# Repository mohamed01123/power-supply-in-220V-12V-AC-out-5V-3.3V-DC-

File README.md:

Universal Power Supply Circuit

This project is an electronic power supply circuit that can be powered by either 12V (AC or DC) or 220V AC, and outputs regulated 5V or 3.3V DC. It includes input protection, voltage regulation, and indicators for status and output selection.

🧩 Features
Dual Input Power:
220V AC (via HLK-PM12 module)
12V input (can be AC or DC)
Selectable Output:
5V or 3.3V regulated DC output
Power Mode Switch:
Toggle between AC or DC mode using a manual switch
Safety Features:
Diodes for reverse polarity protection (especially for 12V DC input)
Bridge rectifier to convert 12V AC to DC
Status Indicator:
LED to indicate that the circuit is powered ON

🔌 Circuit Components
HLK-PM12 : AC-DC module to convert 220V AC to 12V DC
Bridge Rectifier: Converts 12V AC input to DC
7805 Regulator: Outputs regulated 5V
7833 Regulator: Outputs regulated 3.3V
2x Electrolytic Capacitors: For filtering and stabilizing DC output
2x Protection Diodes: Prevents damage if user reverses DC input polarity
Power Mode Switch: Selects between AC and DC input modes
Output Selector Socket: Allows user to choose between 5V and 3.3V output
3x Sockets: 1 for 220V AC input, 1 for 12V input (AC/DC), 1 for output
Power Indicator LED: Lights up when power is supplied to the circuit

⚙️ Working Principle
1-Input:
  If using 220V AC, the circuit powers through HLK-PM12, which outputs 12V DC.
  If using 12V, it can be AC or DC:
  AC: Passed through a bridge rectifier.
  DC: Goes directly to the regulators, with diode protection in case of reversed polarity.
2-Stabilization:
  Capacitors filter and stabilize the voltage before reaching the regulators.
  Output Regulation:
  You can select between 5V (via 7805) or 3.3V (via 7833) using a selector socket.
3-LED Indicator:
  A simple LED indicates that the circuit is powered and active.

🛠️ Use Cases
Powering microcontrollers (like Arduino or ESP8266)
Embedded systems
Low voltage control circuits
DIY electronics projects needing stable 5V or 3.3V

📦 Files in This Repo
README.md — You’re reading it now
circuit_diagram — 

🧠 Notes
Always double-check your power source before switching modes.
Make sure proper heat sinking is used for the regulators if high current is expected.
DO NOT touch the board while connected to 220V AC for safety.

.

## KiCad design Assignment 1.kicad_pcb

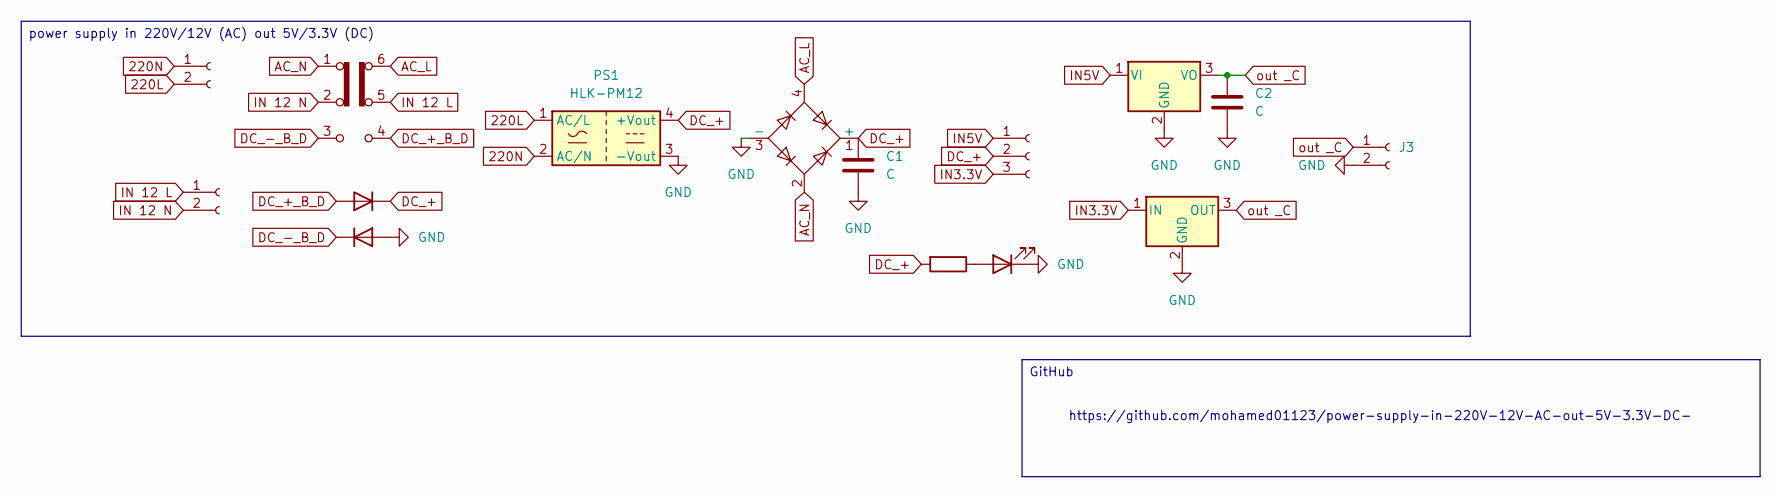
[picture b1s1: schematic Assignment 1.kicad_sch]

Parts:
C1, C2: C; CP_Radial_D4.0mm_P1.50mm
D1, D4: D; D_A-405_P7.62mm_Horizontal
D2: W01G; Diode_Bridge_Round_D9.8mm
D3: LED; LED_D3.0mm
J1, J3, J4: Conn_01x02_Socket; TerminalBlock_Phoenix_MKDS-1,5-2-5.08_1x02_P5.08mm_Horizont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
J2: Conn_01x03_Socket; PinHeader_1x03_P2.54mm_Vertical
PS1: HLK-PM12; Converter_ACDC_Hi-Link_HLK-PMxx
R1: 330; R_Axial_DIN0207_L6.3mm_D2.5mm_P7.62mm_Horizontal
SW3: SW_Slide_DPDT; SW_CK_JS202011CQN_DPDT_Straight
U1: LM7805_TO220; TO-220-3_Vertical
U2: R-783.3-1.0; Converter_DCDC_RECOM_R-78E-0.5_THT

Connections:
220L: J4.2, PS1.1 (AC/L)
220N: J4.1, PS1.2 (AC/N)
AC_L: D2.4, SW3.6 (C)
AC_N: D2.2, SW3.1 (A)
DC_+: C1.1, D2.1 (+), D4.1 (K), J2.2, PS1.4 (+Vout), R1.2
DC_+_B_D: D4.2 (A), SW3.4 (A)
DC_-_B_D: D1.1 (K), SW3.3 (C)
GND: C1.2, C2.2, D1.2 (A), D2.3 (-), D3.1 (K), J3.2, PS1.3 (-Vout), U1.2 (GND), U2.2 (GND)
IN3.3V: J2.3, U2.1 (IN)
IN5V: J2.1, U1.1 (VI)
IN 12 L: J1.1, SW3.5 (B)
IN 12 N: J1.2, SW3.2 (B)
unnamed: D3.2 (A), R1.1
out _C: C2.1, J3.1, U1.3 (VO), U2.3 (OUT)

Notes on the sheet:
https://github.com/mohamed01123/power-supply-in-220V-12V-AC-out-5V-3.3V-DC-
power supply in 220V/12V (AC) out 5V/3.3V (DC)
GitHub

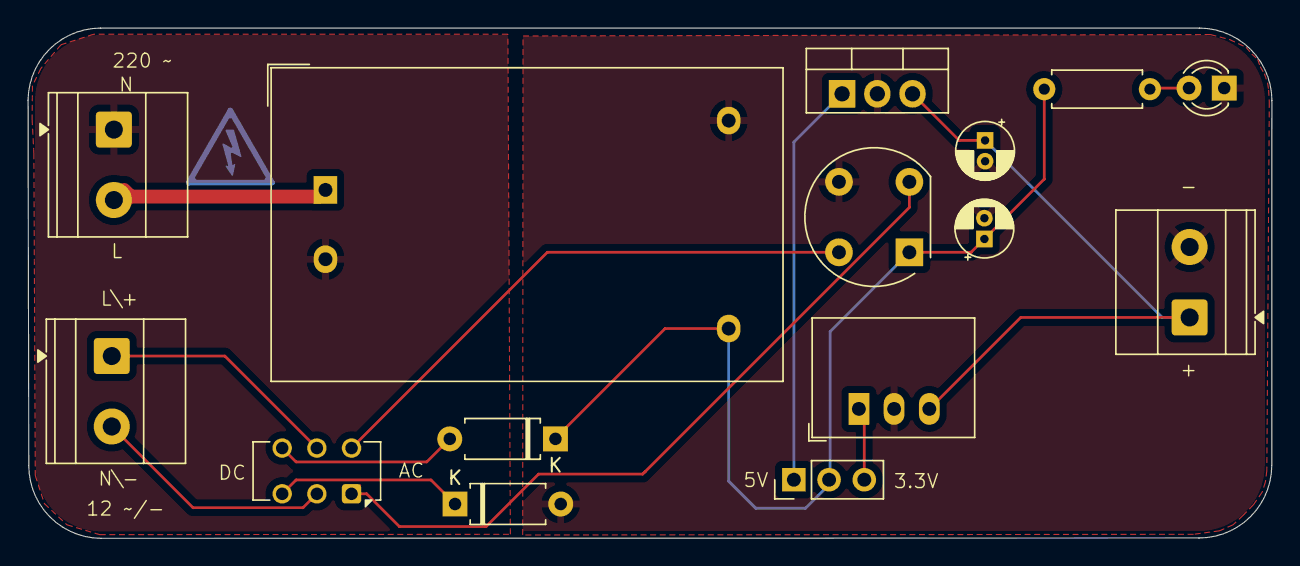
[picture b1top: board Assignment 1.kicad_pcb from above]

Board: 2 copper layers, 89.7 x 36.8 mm, 15 parts (0 on the bottom side), 14 nets.

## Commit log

2025-05-23 frist commit
